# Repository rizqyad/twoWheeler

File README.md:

# twoWheeler
Robot with two wheels.
Component:
- Arduino UNO
- gy-87 [10Dof IMU sensor]
- L298N [H-Bridge Motor Driver Module]
- 2 x DC Motor with rotary encoder

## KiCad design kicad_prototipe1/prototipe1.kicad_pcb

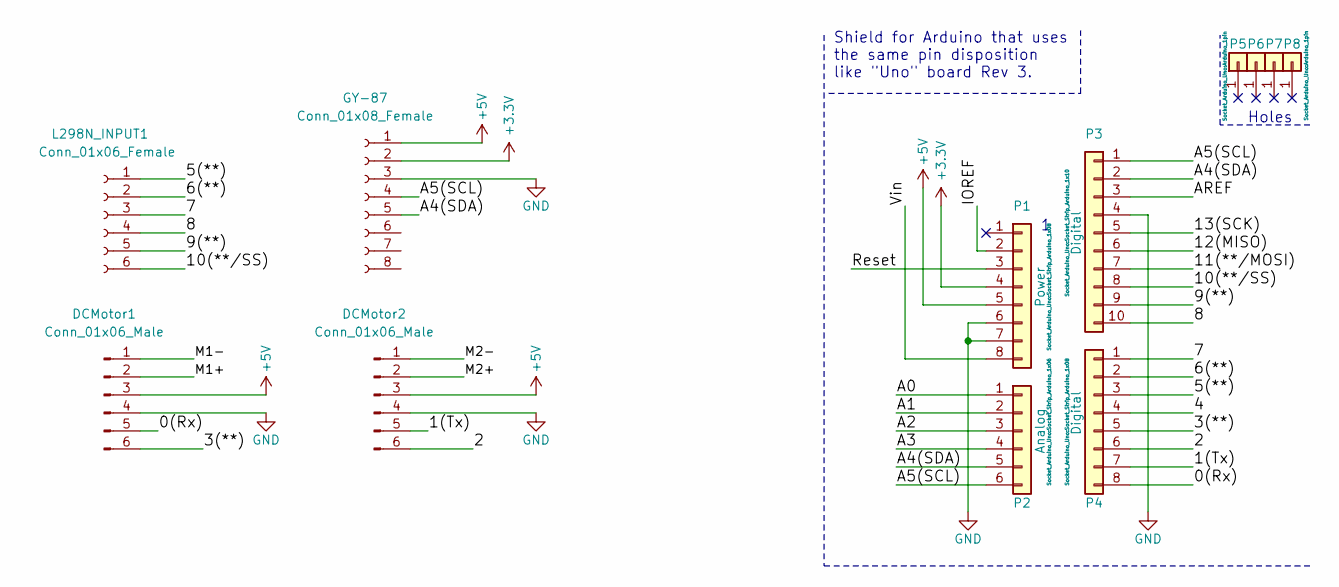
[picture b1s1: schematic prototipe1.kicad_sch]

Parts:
DCMotor1, DCMotor2: Conn_01x06_Male; PinHeader_1x06_P2.54mm_Vertical
GY-87: Conn_01x08_Female; PinSocket_1x08_P2.54mm_Vertical
L298N_INPUT1: Conn_01x06_Female; PinSocket_1x06_P2.54mm_Vertical
P1: Power; Socket_Strip_Arduino_1x08
P2: Analog; Socket_Strip_Arduino_1x06
P3: Digital; Socket_Strip_Arduino_1x10
P4: Digital; Socket_Strip_Arduino_1x08
P5, P6, P7, P8: CONN_01X01; Arduino_1pin

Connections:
+3V3: GY-87.2, P1.4
+5V: DCMotor1.3, DCMotor2.3, GY-87.1, P1.5
/0(Rx): DCMotor1.5, P4.8
/1(Tx): DCMotor2.5, P4.7
/2: DCMotor2.6, P4.6
/3(**): DCMotor1.6, P4.5
/4: P4.4
/5(**): L298N_INPUT1.1, P4.3
/6(**): L298N_INPUT1.2, P4.2
/7: L298N_INPUT1.3, P4.1
/8: L298N_INPUT1.4, P3.10
/9(**): L298N_INPUT1.5, P3.9
/10(**/SS): L298N_INPUT1.6, P3.8
/11(**/MOSI): P3.7
/12(MISO): P3.6
/13(SCK): P3.5
/A0: P2.1
/A1: P2.2
/A2: P2.3
/A3: P2.4
/A4(SDA): GY-87.5, P2.5, P3.2
/A5(SCL): GY-87.4, P2.6, P3.1
/AREF: P3.3
/IOREF: P1.2
/M1+: DCMotor1.2
/M1-: DCMotor1.1
/M2+: DCMotor2.2
/M2-: DCMotor2.1
/Reset: P1.3
/Vin: P1.8
GND: DCMotor1.4, DCMotor2.4, GY-87.3, P1.6, P1.7, P3.4

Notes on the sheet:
Holes
Shield for Arduino that uses the same pin disposition like "Uno" board Rev 3.

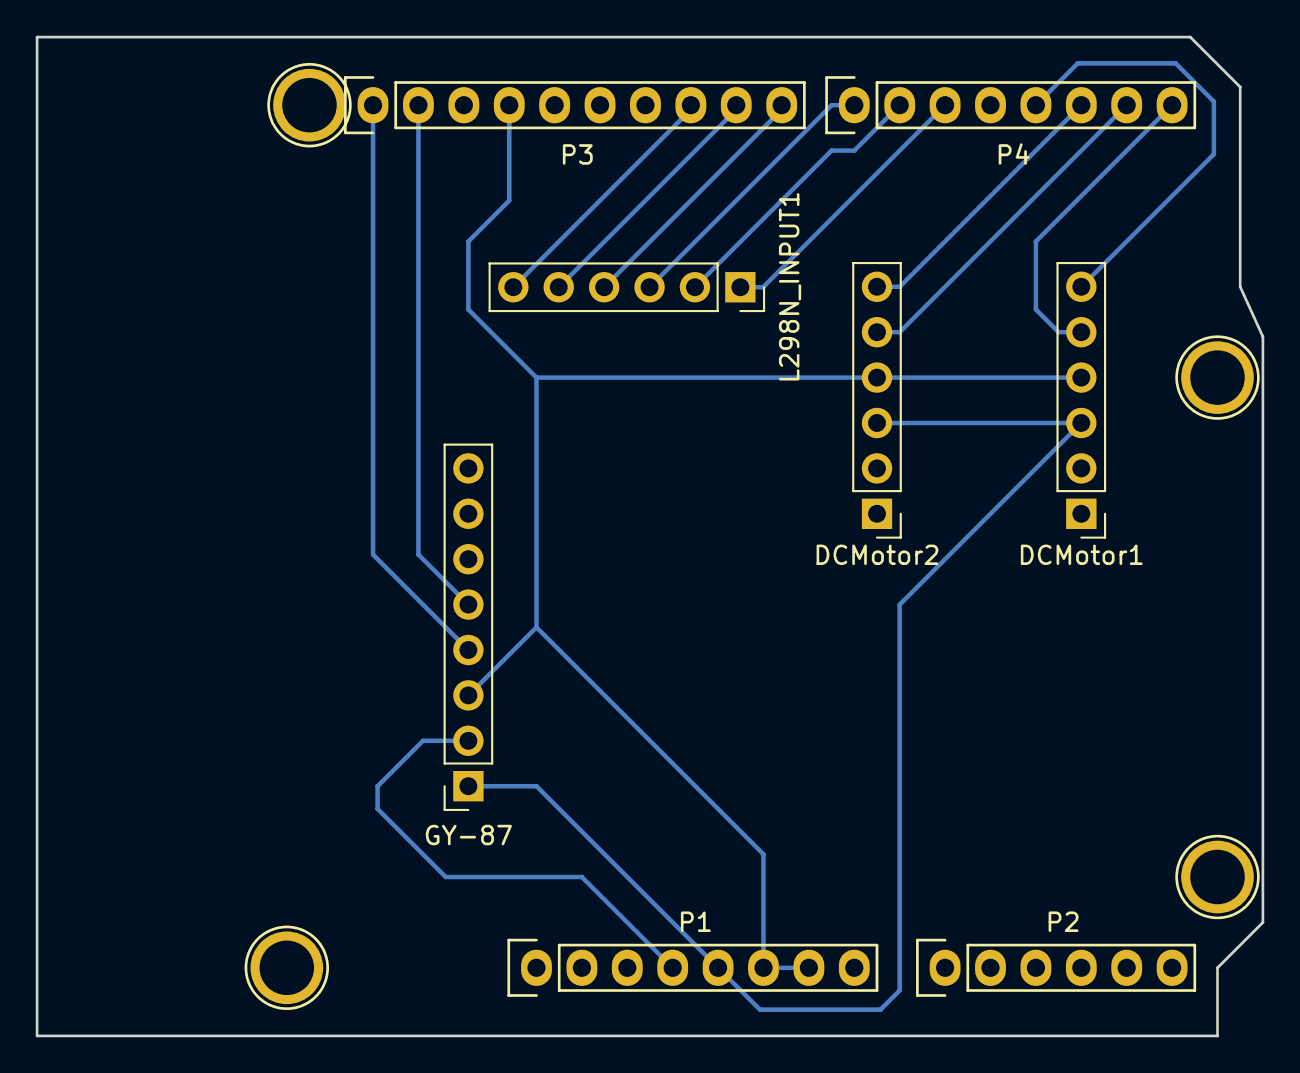
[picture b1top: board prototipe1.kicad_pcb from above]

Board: 2 copper layers, 68.6 x 55.9 mm, 12 parts (0 on the bottom side), 15 nets.

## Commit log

2022-05-10 add project's files
2022-05-11 Modified .fzz
2022-05-11 add sensor IMU
2022-05-11 better lib management
2022-05-11 mainPro.ino modified
2022-05-12 Fix device ID check response
2022-05-12 update kicad prototipe1
2022-05-14 New Config for Motor
2022-05-14 small update
2022-05-15 No PID
2022-05-16 Add Kalman Filter
2022-05-16 Add PID for Motor[not tuned yet]
2022-05-17 increase Kd to reduce overshoot
2022-05-23 some little changes
